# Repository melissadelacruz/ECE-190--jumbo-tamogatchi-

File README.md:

# ECE 190 Project

This is my repo for my ECE 190 project. I will be integrating things such as machine learning, DSP, data analysis, and etc to make this project. I want to be off of of social media and to do so I will focus on creating a physical device that I can use when I have digital fatigue.
Below is a Google drive link that includes other types of documentation for this project. 

Thanks! :D

https://drive.google.com/drive/folders/1MEKUAmXFv2e_WvpG6FI-sjovKOeH6pkQ?usp=drive_link

## ESP32-S3 SPI OLED Test Branch

This branch contains initial firmware testing for:

- ESP32-S3 Mini Dev Board
- 0.96" SPI OLED (SSD1306/SH1106)
- PlatformIO project structure

Pin mapping used:

Screen:  
D0 (SCK)  → GPIO 11  
D1 (MOSI) → GPIO 10  
CS        → GPIO 7  
DC        → GPIO 8  
RES       → GPIO 9  
VCC       → 3.3V

Buttons:  
One End → GND  
Other End → GPIO 5  

One End → GND  
Other End GPIO 4

Library: U8g2  
Framework: Arduino (PlatformIO)

Purpose:
Initial display bring-up and modular firmware structure test.

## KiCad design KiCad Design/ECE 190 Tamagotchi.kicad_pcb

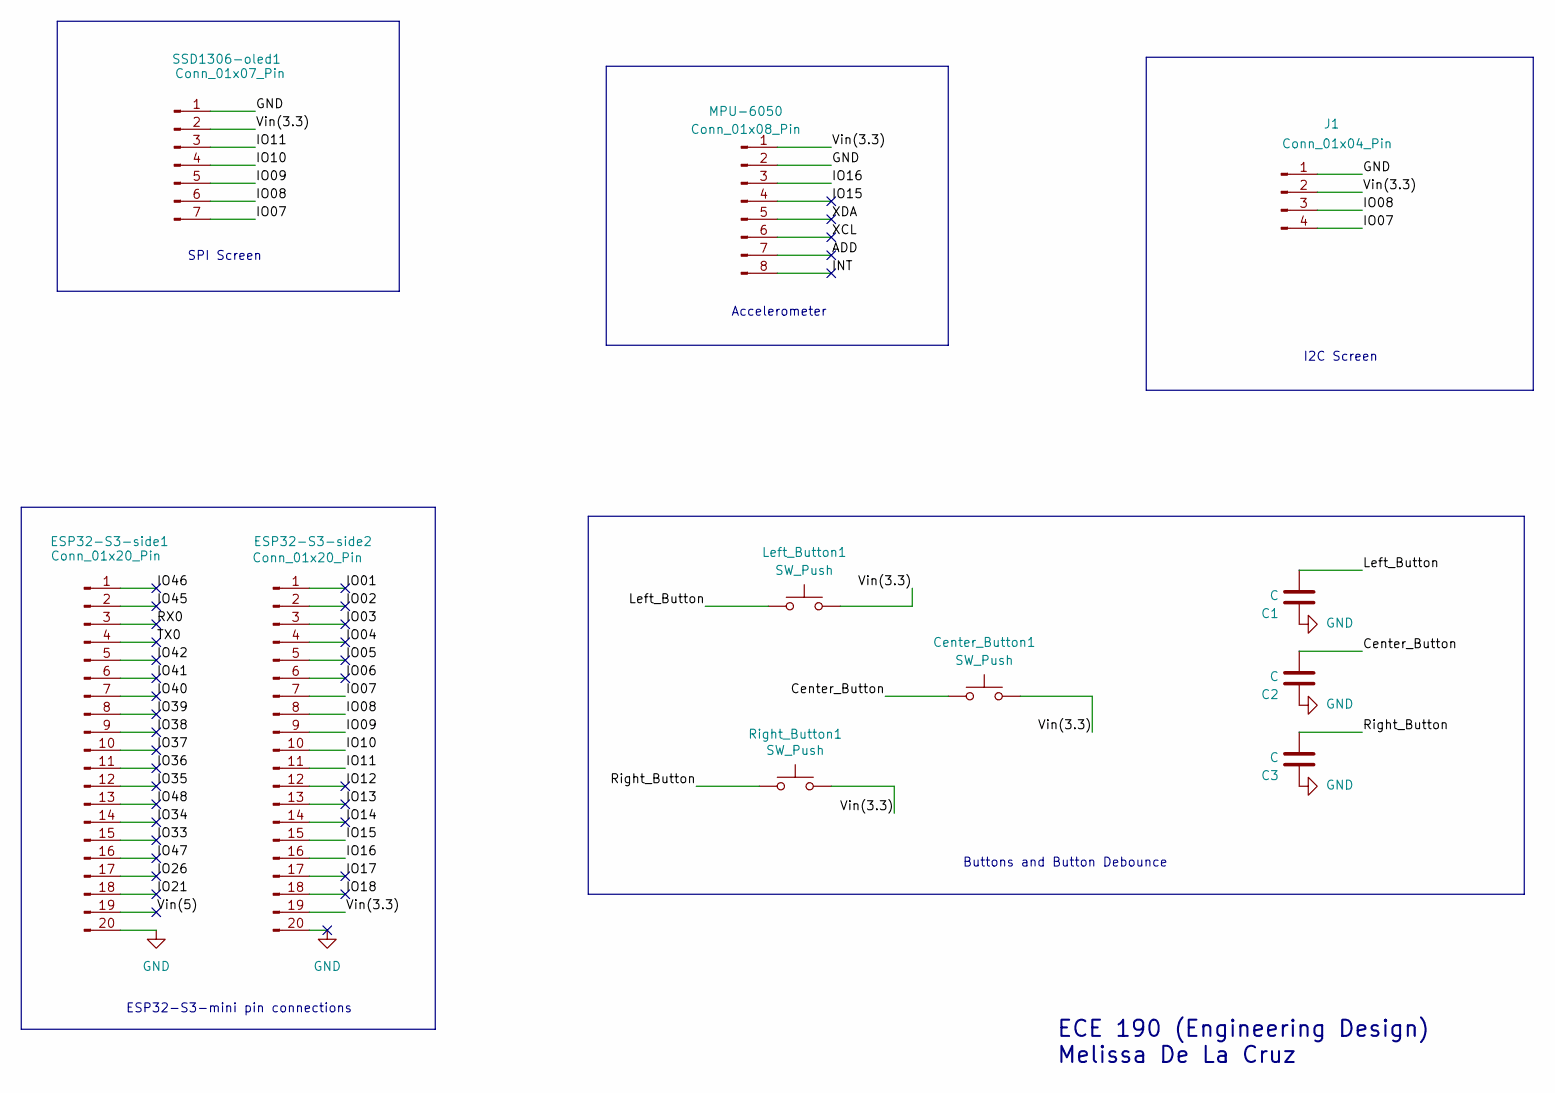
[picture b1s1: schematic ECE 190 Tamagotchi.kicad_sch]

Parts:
C1, C2, C3: C; C_0805_2012Metric_Pad1.18x1.45mm_HandSolder
Center_Button1: SW_Push; SW_SPST_PTS810
ESP32-S3-side1, ESP32-S3-side2: Conn_01x20_Pin; PinHeader_1x20_P2.54mm_Vertical
J1: Conn_01x04_Pin; PinHeader_1x04_P2.54mm_Vertical
Left_Button1: SW_Push; SW_SPST_PTS810
MPU-6050: Conn_01x08_Pin; PinHeader_1x08_P2.54mm_Vertical
Right_Button1: SW_Push; SW_SPST_PTS810
SSD1306-oled1: Conn_01x07_Pin; PinHeader_1x07_P2.54mm_Vertical

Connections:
/ADD: MPU-6050.7
/Center_Button: C2.1, Center_Button1.1
/INT: MPU-6050.8
/IO01: ESP32-S3-side2.1
/IO02: ESP32-S3-side2.2
/IO03: ESP32-S3-side2.3
/IO04: ESP32-S3-side2.4
/IO05: ESP32-S3-side2.5
/IO06: ESP32-S3-side2.6
/IO07: ESP32-S3-side2.7, J1.4, SSD1306-oled1.7
/IO08: ESP32-S3-side2.8, J1.3, SSD1306-oled1.6
/IO09: ESP32-S3-side2.9, SSD1306-oled1.5
/IO10: ESP32-S3-side2.10, SSD1306-oled1.4
/IO11: ESP32-S3-side2.11, SSD1306-oled1.3
/IO12: ESP32-S3-side2.12
/IO13: ESP32-S3-side2.13
/IO14: ESP32-S3-side2.14
/IO15: ESP32-S3-side2.15, MPU-6050.4
/IO16: ESP32-S3-side2.16, MPU-6050.3
/IO17: ESP32-S3-side2.17
/IO18: ESP32-S3-side2.18
/IO21: ESP32-S3-side1.18
/IO26: ESP32-S3-side1.17
/IO33: ESP32-S3-side1.15
/IO34: ESP32-S3-side1.14
/IO35: ESP32-S3-side1.12
/IO36: ESP32-S3-side1.11
/IO37: ESP32-S3-side1.10
/IO38: ESP32-S3-side1.9
/IO39: ESP32-S3-side1.8
/IO40: ESP32-S3-side1.7
/IO41: ESP32-S3-side1.6
/IO42: ESP32-S3-side1.5
/IO45: ESP32-S3-side1.2
/IO46: ESP32-S3-side1.1
/IO47: ESP32-S3-side1.16
/IO48: ESP32-S3-side1.13
/Left_Button: C1.1, Left_Button1.1
/RX0: ESP32-S3-side1.3
/Right_Button: C3.1, Right_Button1.1
/TX0: ESP32-S3-side1.4
/Vin(3.3): Center_Button1.2, ESP32-S3-side2.19, J1.2, Left_Button1.2, MPU-6050.1, Right_Button1.2, SSD1306-oled1.2
/Vin(5): ESP32-S3-side1.19
/XCL: MPU-6050.6
/XDA: MPU-6050.5
GND: C1.2, C2.2, C3.2, ESP32-S3-side1.20, ESP32-S3-side2.20, J1.1, MPU-6050.2, SSD1306-oled1.1

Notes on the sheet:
ECE 190 (Engineering Design) Melissa De La Cruz
I2C Screen
ESP32-S3-mini pin connections
Accelerometer
SPI Screen
Buttons and Button Debounce

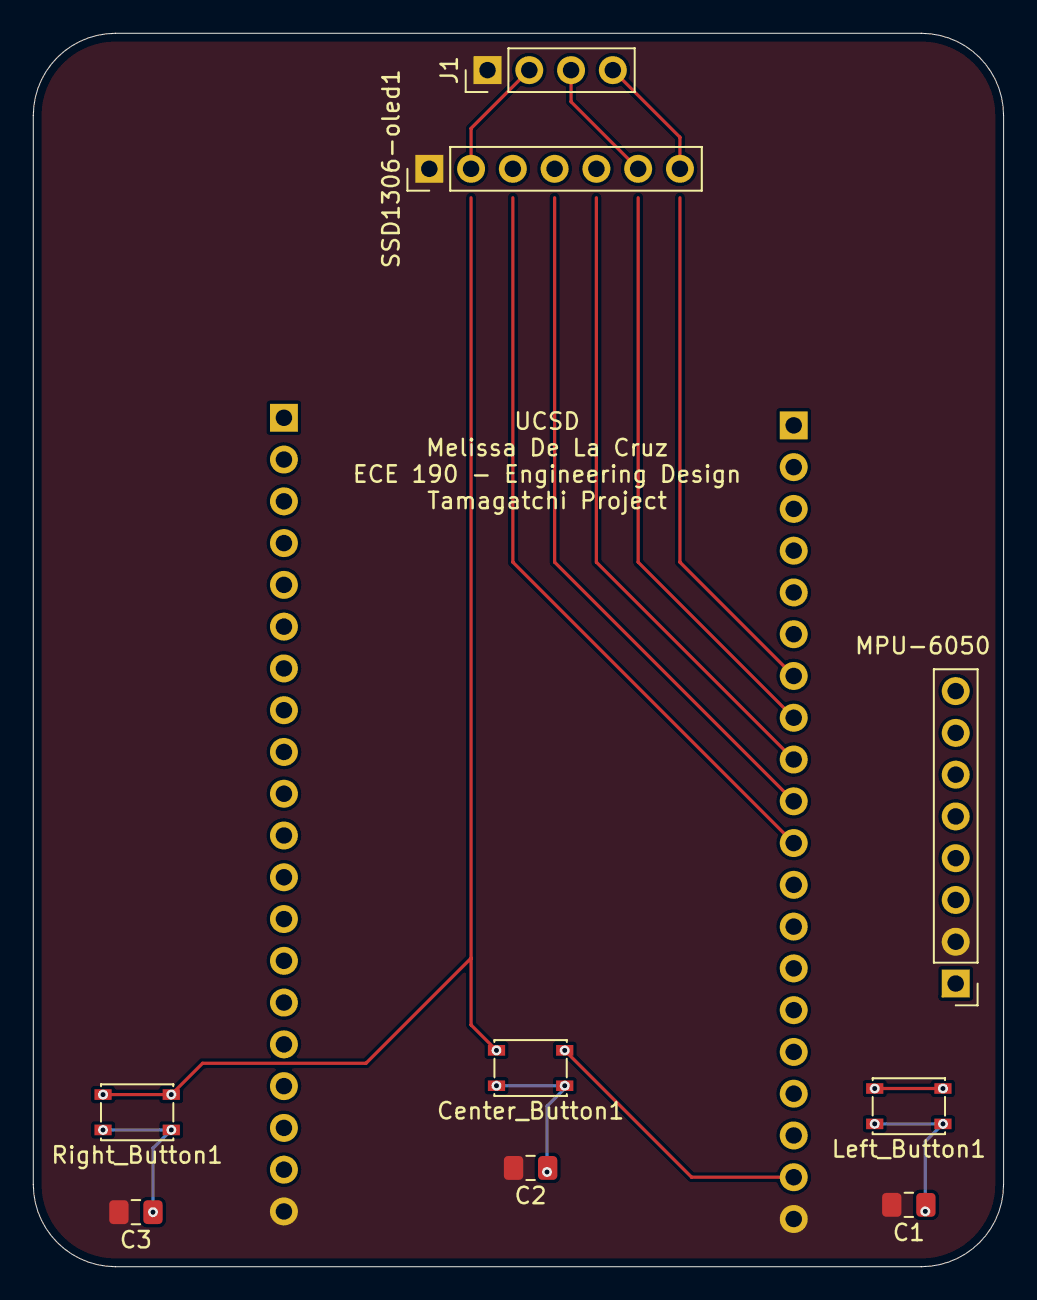
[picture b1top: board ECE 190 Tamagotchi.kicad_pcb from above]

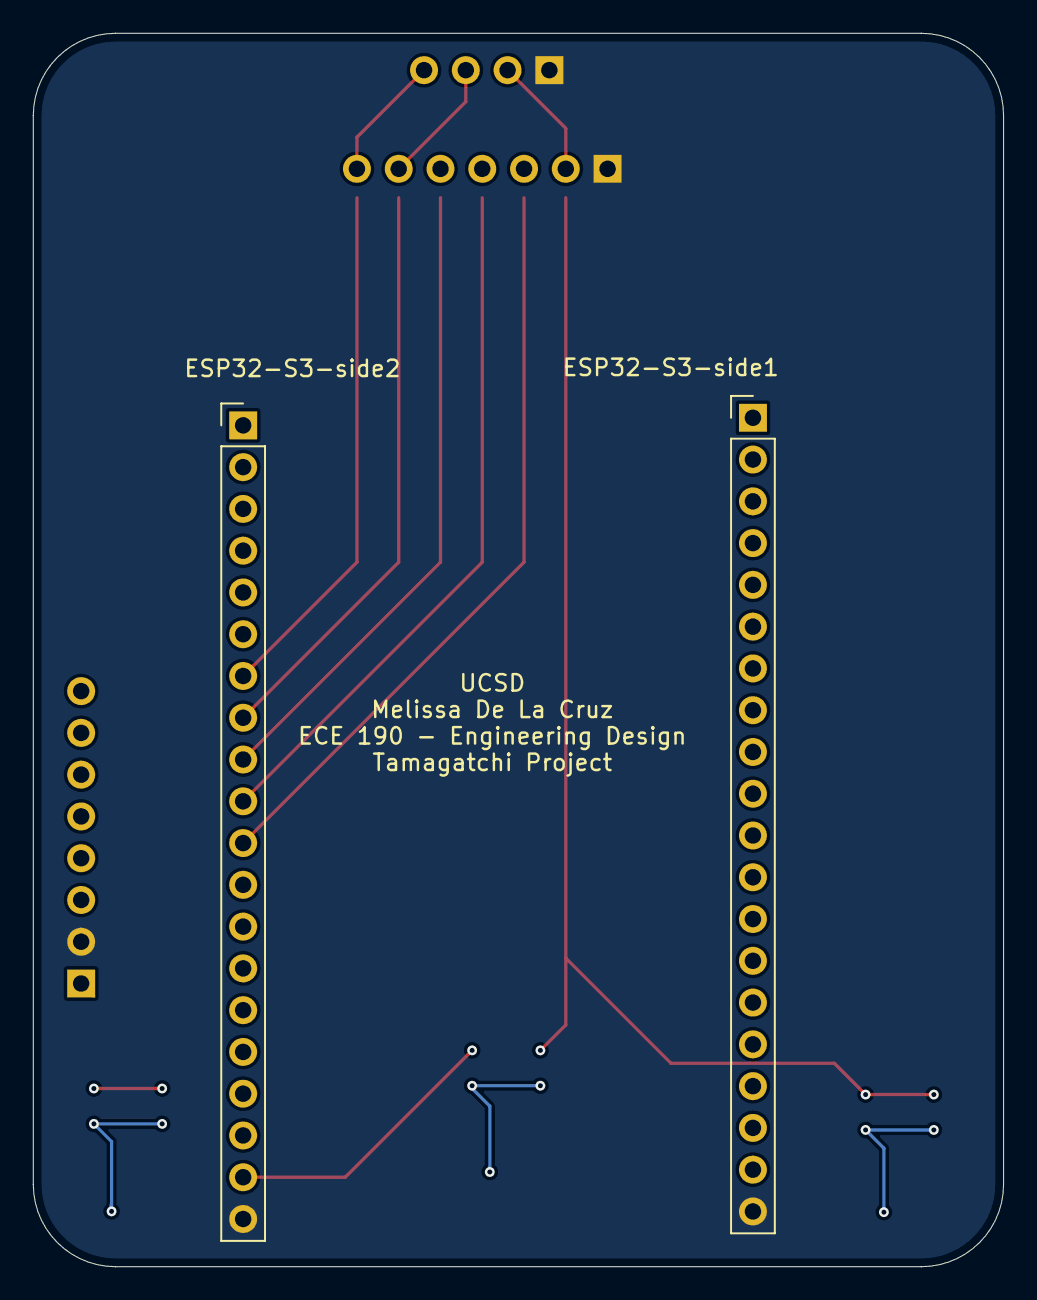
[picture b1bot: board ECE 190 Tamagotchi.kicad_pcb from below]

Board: 2 copper layers, 59.0 x 75.0 mm, 11 parts (2 on the bottom side), 12 nets.

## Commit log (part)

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2026-02-11 readings from accelerometer
    records data from the accelerometer
2026-02-12 added UX flowchart for beginning user
2026-02-19 Initialize README with project details
    Added project overview and documentation link.
2026-02-22 added pin finder for ESP32-s3
    needed to set up screen (SPI)
2026-02-22 moved to folder
2026-02-23 finished adding code to display simple message
2026-02-23 Add initial README for ESP32-S3 SPI OLED testing
    This README outlines the initial firmware testing for the ESP32-S3 Mini Dev Board with a 0.96" SPI OLED, including pin mappings and project structure.
2026-02-23 Correct pin mapping formatting in README
    Fix formatting issues in the pin mapping section.
2026-02-23 Fix duplicate VCC entry in README
    Removed duplicate VCC entry in pin mapping section.
2026-02-25 Update README with button pin mapping
    Added pin mapping details for buttons in README.
2026-02-25 updated accelerometer pins
2026-02-25 updated pins
2026-02-27 added KiCad design
    Could not figure out how to do the spacing (measurements), but tried my best to visually inspect it
2026-03-09 added ui for pet, happy pet
2026-03-11 added button functions for all three buttons
2026-03-11 Fix button wiring details in README
    Correct button wiring instructions for GPIO connections.
2026-03-18 got serial monitor to work with platformio
2026-03-18 added play mode with step counter (needs to be debugged)
2026-03-18 fixed ui for play mode (need to figure out heart placement)
2026-03-18 changed ui for play button as well as added feature of pressing twice to go back to homepage
2026-03-18 added real time and date
2026-03-19 display on TFT SPI 4.0 screen
    displays blue and red transition. This was a big obstacle for me to get working, and I got it to work. (a bit side tracked as Friday is the last day and its wednesday)
2026-03-19 Create files to delete to get SPI_TFT to work.png
    files to delete.
2026-03-19 fixing exposed key issue
2026-03-21 fixed pin assignment on accelerometer
2026-03-22 updated button features (added shake feature to feed)
2026-03-23 fixed shake feature and other UI features
2026-03-23 updated pedometer (more accurate)
2026-03-23 finished fixing issue with mood meter and feed meter (added happy meter)
2026-03-23 finished code (might still need to be cleaned up for SWE standards)
2026-03-23 Comment out all code in testing_tft_spi.ino
    Comment out the entire code for testing purposes.
2026-03-23 Comment out accelerometer data collection code
    Comment out the entire accelerometer data collection code (for testing pin connection).
2026-03-23 Comment out setup and loop functions
    Comment out the setup and loop functions for testing.
2026-04-15 added debug for wifi connection
2026-04-15 added 3 button feature to reset all mood bars
